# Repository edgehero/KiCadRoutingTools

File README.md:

# gpm campaign assets: 20 boards through `/plan-pcb-placement full` on KiCadRoutingTools main bda59fa0

Results are in discussion #118 (drandyhaas/KiCadRoutingTools). This branch holds what the post links to.

- `media/NN_STEM/`: per board:
  - the movie3d films (`film_seed.*`, the kept seed's anneal; `film_flow.*`, the whole run, where it tells the run's story);
  - the 3D stills, and the human-vs-ours placement comparisons;
  - the teammate's `REPORT.md`, `TOOL_GAPS.md` and `CHOSEN.json`;
  - what it was given (`README.md`);
  - my grades (`summary.json`, `grade_ours.json`, `board_score.json`);
  - the delivered board.
- `media/_superseded/`: the first runs of daplink and steppenprobe, which were re-run after the audit.
- `wk/gpm/`: every `wk/gpm/...` path the findings and issues cite, at the same path. Copy `wk/` into a checkout at bda59fa0 and run the repro commands from the root.
- `FINDINGS.md`: every verifier verdict (G01-G47, M01-M16). `FINDINGS_CLUSTERED.md` holds the clusters before verification, and `verify/` the batch reports and prompts.
- `old_issues/`: gp14's 65 issues re-checked on main (`OLD_ISSUES.md`, `B1.md`-`B8.md`).
- `AUDIT.md` and `audit/`: the start-state, copying and transcript audit, with its scripts and outputs.
- `issues/`: the issue drafts as filed.
- `staging/`: the campaign scripts (staging, teammate prompt, compare, films, post).
- `GRADE_NOTES.md`, `LAUNCH.md`, `PHASE0.md`, `STAGING_DIFF.md`, `FINDINGS_PREP.md`: the lead's own notes.

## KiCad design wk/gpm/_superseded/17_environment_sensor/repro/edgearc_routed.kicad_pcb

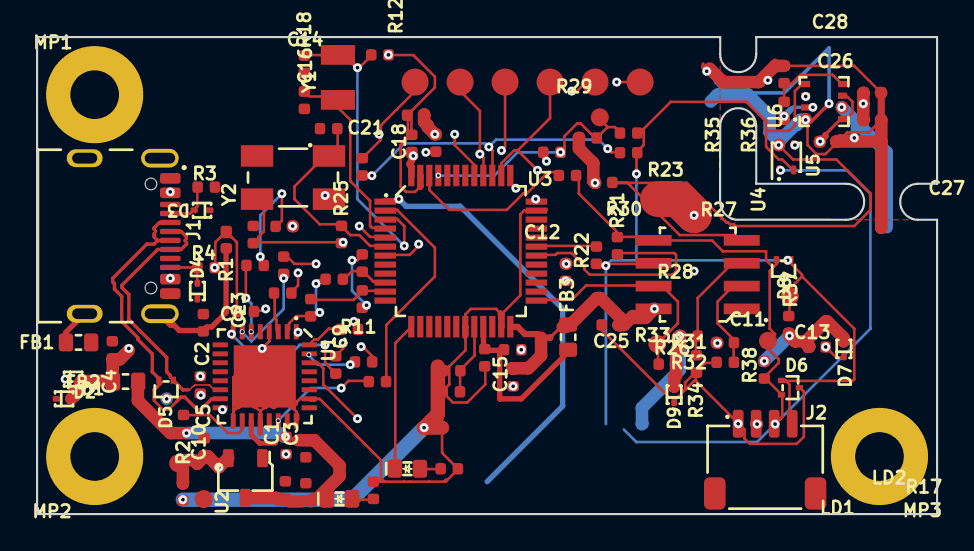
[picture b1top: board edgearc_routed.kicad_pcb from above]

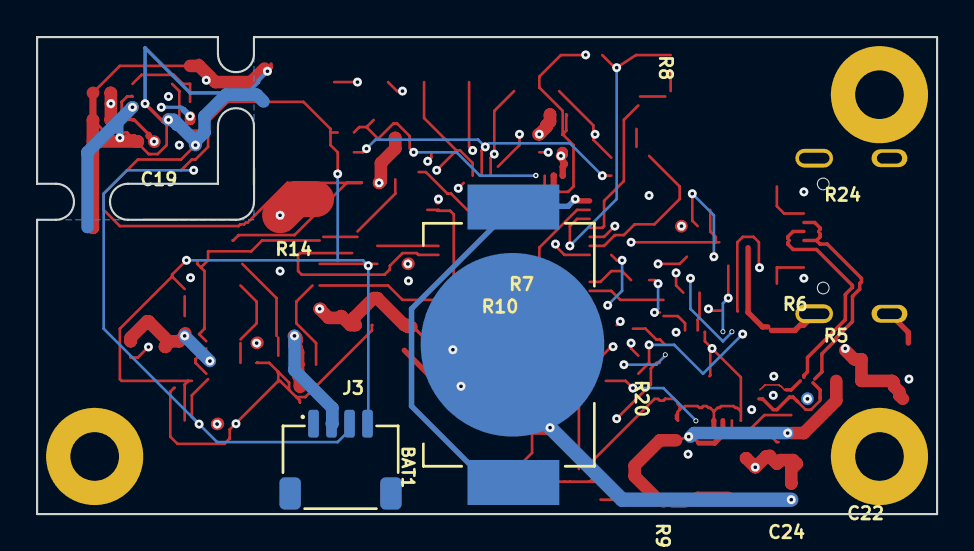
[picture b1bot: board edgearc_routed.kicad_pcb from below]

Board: 4 copper layers, 50.0 x 26.5 mm, 107 parts (2 on the bottom side), 50 nets.

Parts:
BAT1: BAT-HLD-012-SMT-TR; BAT_BAT-HLD-012-SMT-TR
C1, C9, C10: C_4u7_0402; C_0402_1005Metric
C2, C3, C5, C6, C8, C12, C13, C15, C17, C18, C19, C22, C25, C26, C27, C28: C_100n_0402; C_0402_1005Metric
C4, C7, C11, C20, C24: C_2u2_0402; C_0402_1005Metric
C14, C16: C_16p_0402; C_0402_1005Metric
C21, C23: C_10p_0402; C_0402_1005Metric
D1, D2, D3, D4, D7, D9: ESD9X5.0ST5G; SOD-923
D5, D6, D8: TPD2E009_SOT-9X3; SOT-723
FB1, FB2, FB3: FB_120Z_2A_Murata-BLM18PG_0603; FB_0603_1608Metric
J1: USB-C_GCT_USB4105-GF-A; USB-C_Receptacle_GCT_USB4105-GF-A
J2, J3: JST_SH_1x4_SM04B-SRSS-TB-LF-SN; Conn_JST_SH_1x4_SM04B-SRSS-TB-LF-SN
LD1, LD2: LED_G_0603_KP-1608ZGC; LED_0603_1608Metric_G
MP1, MP2, MP3: MP_Pad5.4mm_Drill2.7mm
R1, R18, R25: R_1M_0402; R_0402_1005Metric
R2, R26: R_1k_0402; R_0402_1005Metric
R3, R4, R37, R38: R_5k1_0402; R_0402_1005Metric
R5, R6, R7, R8, R9, R10, R11, R13, R14, R15, R16, R20: R_0R_0402; R_0402_1005Metric
R12, R17: R_470R_0402; R_0402_1005Metric
R19, R24, R29, R30, R31, R32, R33, R34, R35, R36: R_100k_0402; R_0402_1005Metric
R21, R22, R23, R27, R28: R_100R_0402; R_0402_1005Metric
TP1, TP2, TP3, TP4, TP5, TP6: TP_1.5mm_SMD; TP_SMD_1.5mm
TP7, TP8, TP9, TP10, TP11, TP12: TP_1mm_SMD; TP_SMD_1mm
U1: FT232R_QFN; QFN-32-1EP_5x5mm
U2: AP7370-33SA-7; SOT-23-3
U3: STM32G474CET6; LQFP-48_7x7mm_P0.5mm
U4: MB85RC1MTPNF-G; SOP-8_3.9x5.05mm_P1.27mm
U5: SHT45; Sensirion_DFN-4-1.5x1.5x0.5mm_P0.8mm
U6: BME280; LGA-8_2.5x2.5mm_BME280
Y1: Resonator_32.768kHz_ECX-31B; Resonator_SMD_ECS_ECX-31B_3.2x1.5x0.9mm
Y2: Resonator_8MHz_ABM3B; Resonator_SMD_Abracon_ABM3B_5x3.2mm

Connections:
+3V3: C9.2, C10.2, C11.1, C12.2, C13.1, C15.2, C17.2, C18.2, C25.1, C26.1, C27.2, C28.1, D7.2 (A), D9.2 (A), FB3.2, J2.2, J3.2, R19.2, R24.2, R26.2, R29.2, R31.2, R33.2, R35.1, R37.2, R38.2, TP9.1, U2.2 (VOUT), U3.24 (VDD), U3.36 (VDD), U3.48 (VDD), U4.8 (VDD), U5.3 (VDD), U6.2 (CSB), U6.6 (VDDIO), U6.8 (VDD)
+5V: C1.2, C3.2, C7.1, C8.1, FB2.2, LD1.1 (C), R2.1, U1.19 (VCC), U2.3 (VIN)
/FRAM_WP: R26.1, TP7.1, U3.25 (PB11), U4.7 (WP)
/FTDI_USER_PB: R11.2, U3.2 (PC13)
/LD2: LD2.1 (C), U3.13 (PA5)
/OSC32_IN: C14.1, R18.1, U3.3 (PC14-OSC32_IN), Y1.1
/OSC32_OUT: C16.1, R18.2, U3.4 (PC15-OSC32_OUT), Y1.2
/USB_CC1: D3.2 (A), J1.A5 (CC_{1}), R3.2
/USB_CC2: D4.2 (A), J1.B5 (CC_{2}), R4.2
/USB_D_N: D5.2, J1.A7 (D_{A}-), J1.B7 (D_{B}-), U1.15 (USBDM)
/USB_D_P: D5.1, J1.A6 (D_{A}+), J1.B6 (D_{B}+), U1.14 (USBDP)
/VBUS: C4.2, D1.2 (A), D2.2 (A), FB2.1, J1.A4 (VBUS), J1.A9 (VBUS), J1.B4 (VBUS), J1.B9 (VBUS)
GND: BAT1.N, C1.1, C2.1, C3.1, C4.1, C5.1, C6.1, C7.2, C8.2, C9.1, C10.1, C11.2, C12.1, C13.2, C14.2, C15.1, C16.2, C17.1, C18.1, C19.2, C20.1, C21.1, C22.2, C23.1, C24.1, C25.2, C26.2, C27.1, C28.2, D1.1 (C), D2.1 (C), D3.1 (C), D4.1 (C), D5.3, D6.3, D7.1 (C), D8.3, D9.1 (C), FB1.2, J1.A1 (GND), J1.A12 (GND), J1.B1 (GND), J1.B12 (GND), J2.1, J3.1, R1.2, R3.1, R4.1, R12.1, R17.1, R30.1, R32.1, R34.1, R36.1, TP10.1, U1.4 (GND), U1.17 (GND), U1.20 (GND), U1.24 (AGND), U1.26 (TEST), U1.33 (EP), U2.1 (GND), U3.19 (VSSA), U3.23 (VSS), U3.35 (VSS), U3.47 (VSS), U4.4 (VSS), U5.4 (VSS), U6.1 (GND), U6.7 (GND), Y2.2 (SH), Y2.4 (SH)
GNDREF: C2.2, FB1.1, J1.SH, R1.1
I2C_1_SCL: D6.1, D8.1, J2.4, J3.4, R22.2, R23.2, R27.2, R37.1, TP12.1, U4.6 (SCL), U5.2 (SCL), U6.4 (SCK)
I2C_1_SDA: D6.2, D8.2, J2.3, J3.3, R21.2, R28.2, R38.1, TP11.1, U4.5 (SDA), U5.1 (SDA), U6.3 (SDI)
JTDI: R10.2, R20.1, TP6.1
JTDO: R9.2, TP5.1, U3.40 (PB3)
JTRST: R7.2, R24.1, TP2.1, U3.41 (PB4)
LPUART_1_STM_RX: R13.2, R16.2, U3.11 (PA3)
LPUART_1_STM_TX: R14.2, R15.2, U3.10 (PA2)
NRST: R8.2, R19.1, TP1.1, U3.7 (PG10-NRST)
unnamed: LD1.2 (A), R12.2
unnamed: LD2.2 (A), R17.2
unnamed: C5.2, C6.2, U1.1 (VCCIO), U1.16 (3V3OUT)
unnamed: R11.1, U1.22 (CBUS0)
unnamed: R9.1, U1.8 (CTS#)
unnamed: R8.1, U1.7 (DCD#)
unnamed: R7.1, U1.6 (DSR#)
unnamed: R5.1, U1.31 (DTR#)
unnamed: R2.2, U1.18 (RESET#)
unnamed: R10.1, U1.3 (RI#)
unnamed: R6.1, U1.32 (RTS#)
unnamed: R14.1, R16.1, U1.2 (RXD)
unnamed: R13.1, R15.1, U1.30 (TXD)
unnamed: R21.1, U3.30 (PA8)
unnamed: R22.1, U3.31 (PA9)
unnamed: R20.2, R23.1, U3.39 (PA15)
unnamed: R27.1, R29.1, R30.2, TP8.1, U3.45 (PB8-BOOT0)
unnamed: R28.1, U3.46 (PB9)
unnamed: C23.2, R25.2, U3.5 (PF0-OSC_IN), Y2.3
unnamed: C21.2, R25.1, U3.6 (PF1-OSC_OUT), Y2.1
unnamed: BAT1.P1, BAT1.P2, U3.1 (VBAT)
unnamed: C19.1, C20.2, FB3.1, U3.21 (VDDA)
unnamed: C22.1, C24.2, U3.20 (VREF+)
unnamed: R31.1, R32.2, U4.2 (A1)
unnamed: R33.1, R34.2, U4.3 (A2)
unnamed: R35.2, R36.2, U6.5 (SDO)
SWCLK-JTCK: R6.2, TP4.1, U3.38 (PA14)
SWDIO-JTMS: R5.2, TP3.1, U3.37 (PA13)

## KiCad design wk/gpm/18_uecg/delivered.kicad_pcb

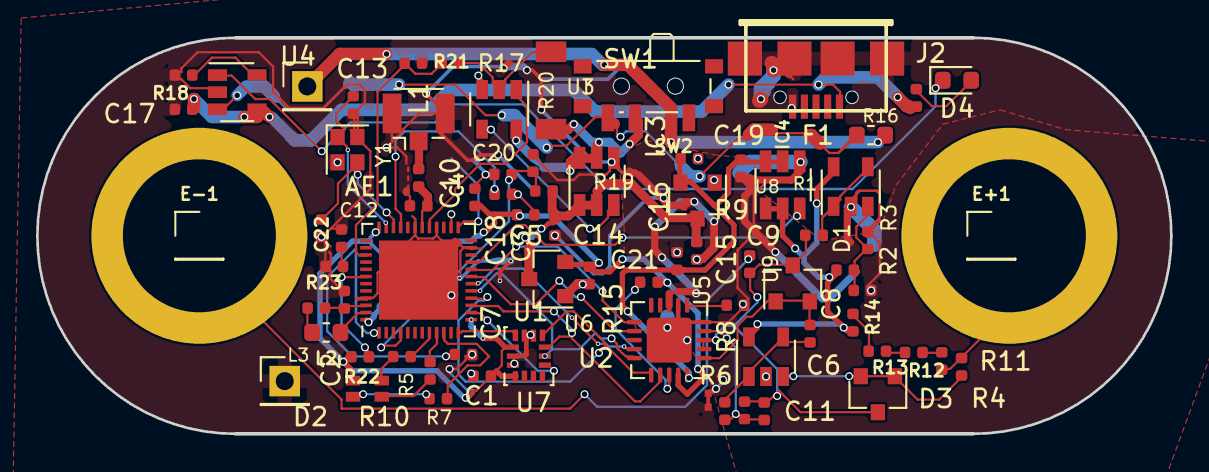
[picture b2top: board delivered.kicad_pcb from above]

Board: 2 copper layers, 63.0 x 22.0 mm, 75 parts (1 on the bottom side), 59 nets.

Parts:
AE1: Antenna_Shield; U.FL_Hirose_U.FL-R-SMT-1_Vertical
C1, C4, C7, C8, C15, C16, C20, C22: 100 nF; C_0402_1005Metric
C2, C14, C17, C18, C19, C21: 2.2 uF; C_0402_1005Metric
C3: 100 pF; C_0402_1005Metric
C5, C6, C9: 10 uF; C_0402_1005Metric
C10: 0.8 pF; C_0402_1005Metric
C11: 10 nF; C_0402_1005Metric
C12, C13: 12 pF; C_0402_1005Metric
D1, D3: BAV99-E3-08; SOT-23
D2: LED_BGRA; LED_RGB_0603_a4
D4: LED GREEN; LED_0603_1608Metric
E+1: Conn_01x01_Male; PinHeader_1x01_P2.54mm_Vertical
E-1: Conn_01x01_Male; PinHeader_1x01_P2.54mm_Vertical
F1: PTC Fuse 0.25A; Fuse_0603_1608Metric
GC1: GND_CONN; 0R_SHUNT
IC3, IC4: SIP32510DT-T1-GE3; TSOT-23-6
J2: USB_B_Micro; conn_usb_B_micro_smd_our
J5: Conn_01x01_Male; Pin_Header_Straight_1x01_Pitch2.54mm
J6: Conn_01x01_Male; PinHeader_1x01_P2.54mm_Vertical
L1: 3.9 nH; L_0402_1005Metric
L2: 10 uH; L_0603_1608Metric
L3: 15 nH; L_0402_1005Metric
R1: 10R; R_0402_1005Metric
R2: 510k; R_0402_1005Metric
R3, R15, R19: 200k; R_0402_1005Metric
R4, R9, R20, R21, R23: 100k; R_0402_1005Metric
R5, R7, R10, R16: 2k; R_0402_1005Metric
R6, R17: 22k; R_0402_1005Metric
R8: 10k; R_0402_1005Metric
R11, R12, R13, R14: 10М; R_0402_1005Metric
R18: 8.2k; R_0402_1005Metric
R22: 100k NTC; R_0402_1005Metric
SC1: SWD_POGO
SW1: SW_Push; BTN_HY_1185
SW2: SW_SPDT; SW_SPDT_PCM12
U1: nRF52832-QFxx; QFN-48-1EP_6x6mm_Pitch0.4mm
U2: MCP3911(QFN); QFN-20-1EP_4x4mm_P0.5mm_EP2.5x2.5mm
U3: 74AHC1G32; SOT-23-5
U4: TP4054_replacement_for_MCP73831-2-OT; SOT-23-5
U5: XC6206P302MR_SOT23; SOT-23
U6: XC6206P332MR_SOT23; SOT-23
U7: LSM6DS3; LGA-14_3x2.5mm_P0.5mm_fix
U8, U9: TLV271CW5; SOT-23-5
Y1: 32MHz; Crystal_SMD_2016-4Pin_2.0x1.6mm

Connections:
+3.3VA: IC4.1 (OUT_1), IC4.2 (OUT_2), R2.2, R14.2, U8.5 (V+), U9.5 (V+)
+3.3VADC: C9.2, C16.2, C19.2, IC4.5 (IN_1), IC4.6 (IN_2), U2.20 (AVdd), U5.2 (VO)
+3V3: C4.1, C5.2, C7.2, C14.2, D2.4 (A), R15.2, R22.1, SC1.2 (3V3), U1.13 (VDD), U1.36 (VDD), U1.48 (VDD), U2.19 (DVdd), U6.2 (VO), U7.5 (VDDIO), U7.8 (VDD)
+4V: IC3.5 (IN_1), IC3.6 (IN_2), SW1.2, SW2.2 (B), U3.5 (VCC)
+BATT: C18.2, C21.2, IC3.1 (OUT_1), IC3.2 (OUT_2), R19.1, U5.3 (VI), U6.3 (VI)
AMP_EN: IC4.3 (EN), U1.21 (P0.18/SWO)
BATT_LEVEL: C20.2, R19.2, R20.1, U1.4 (P0.02/AIN0)
BT_OUT: R17.1, SW1.1, U3.2
CH0+: C6.2, D1.1 (A), D1.2 (K), U2.1 (CH0+)
CH0-: C11.2, D1.3 (A), D3.3 (A), R1.1, R8.1, R9.1, U2.2 (CH0-), U2.3 (CH1-)
CH1+: C11.1, R6.1, R8.2, U2.4 (CH1+)
CIPO: U1.16 (P0.13), U2.16 (MISO), U7.1 (SDO/SA0)
COPI: U1.15 (P0.12), U2.17 (MOSI), U7.14 (SDA)
CS: U1.18 (P0.15), U2.14 (CS)
DR: U1.20 (P0.17), U2.11 (DR)
F_CLK: U1.19 (P0.16), U2.12 (OSC1/CLK)
GND: AE1.2 (Shield), C1.2, C2.2, C3.2, C4.2, C5.1, C7.1, C10.2, C12.1, C13.1, C14.1, C17.1, C18.1, C20.1, C21.1, C22.1, GC1.1, IC3.4 (GND), J2.5 (GND), J2.6 (Shield), J6.1, R18.2, R20.2, R21.2, R23.2, SC1.1 (GND), U1.23 (P0.20), U1.28 (P0.23), U1.31 (VSS), U1.45 (VSS), U1.49 (VSS), U2.8 (Dgnd), U3.3 (GND), U4.2 (VSS), U6.1 (GND), U7.2 (SDX), U7.3 (SCX), U7.6 (GND), U7.7 (GND), Y1.2, Y1.4
GNDA: C8.1, C9.1, C15.1, C16.1, C19.1, GC1.2, IC4.4 (GND), R3.1, U2.5 (Agnd), U2.7 (REFIN-), U2.21 (EP), U5.1 (GND), U8.2 (V-), U9.2 (V-)
IN2: D3.1 (A), D3.2 (K), R4.1, U9.3 (+)
LSM_CS: U1.14 (P0.11), U7.12 (CS)
LSM_INT: U1.12 (NFC2/P0.10), U7.4 (INT1)
NTC_REF: C22.2, R22.2, R23.1, U1.42 (P0.30/AIN6)
unnamed: AE1.1 (A), L1.1
unnamed: C1.1, U1.1 (DEC1)
unnamed: C2.1, L3.2, U1.46 (DEC4)
unnamed: C3.1, U1.33 (DEC3)
unnamed: C6.1, R6.2, U9.1, U9.4 (-)
unnamed: C8.2, R2.1, R3.2, U8.3 (+)
unnamed: C10.1, L1.2, U1.30 (ANT)
unnamed: C12.2, U1.34 (XC1), Y1.3
unnamed: C13.2, U1.35 (XC2), Y1.1
unnamed: C15.2, U2.6 (REFIN+)
unnamed: C17.2, J2.1 (VBUS), R16.2, U4.4 (VDD)
unnamed: D2.1 (BK), R10.1
unnamed: D2.2 (GK), R7.1
unnamed: D2.3 (RK), R5.1
unnamed: D4.1 (K), U4.1 (STAT)
unnamed: D4.2 (A), R16.1
unnamed: E+1.1, R4.2, R11.1
unnamed: E-1.1, R9.2
unnamed: F1.1, SW2.3 (C), U4.3 (VBAT)
unnamed: F1.2, J5.1
unnamed: IC3.3 (EN), U3.4
unnamed: L2.1, U1.47 (DCC)
unnamed: L2.2, L3.1
unnamed: R1.2, U8.1, U8.4 (-)
unnamed: R5.2, U1.8 (P0.06)
unnamed: R7.2, U1.9 (P0.07)
unnamed: R10.2, U1.10 (P0.08)
unnamed: R11.2, R12.1
unnamed: R12.2, R13.1
unnamed: R13.2, R14.1
unnamed: R15.1, U2.18 (RESET)
unnamed: R17.2, R21.1, U1.39 (P0.27)
unnamed: R18.1, U4.5 (PROG)
SCLK: U1.17 (P0.14), U2.15 (SCK), U7.13 (SCL)
SWDCLK: SC1.4 (SWDCLK), U1.25 (SWDCLK)
SWDIO: SC1.3 (SWDIO), U1.26 (SWDIO)
SYS_ON: U1.29 (P0.24), U3.1

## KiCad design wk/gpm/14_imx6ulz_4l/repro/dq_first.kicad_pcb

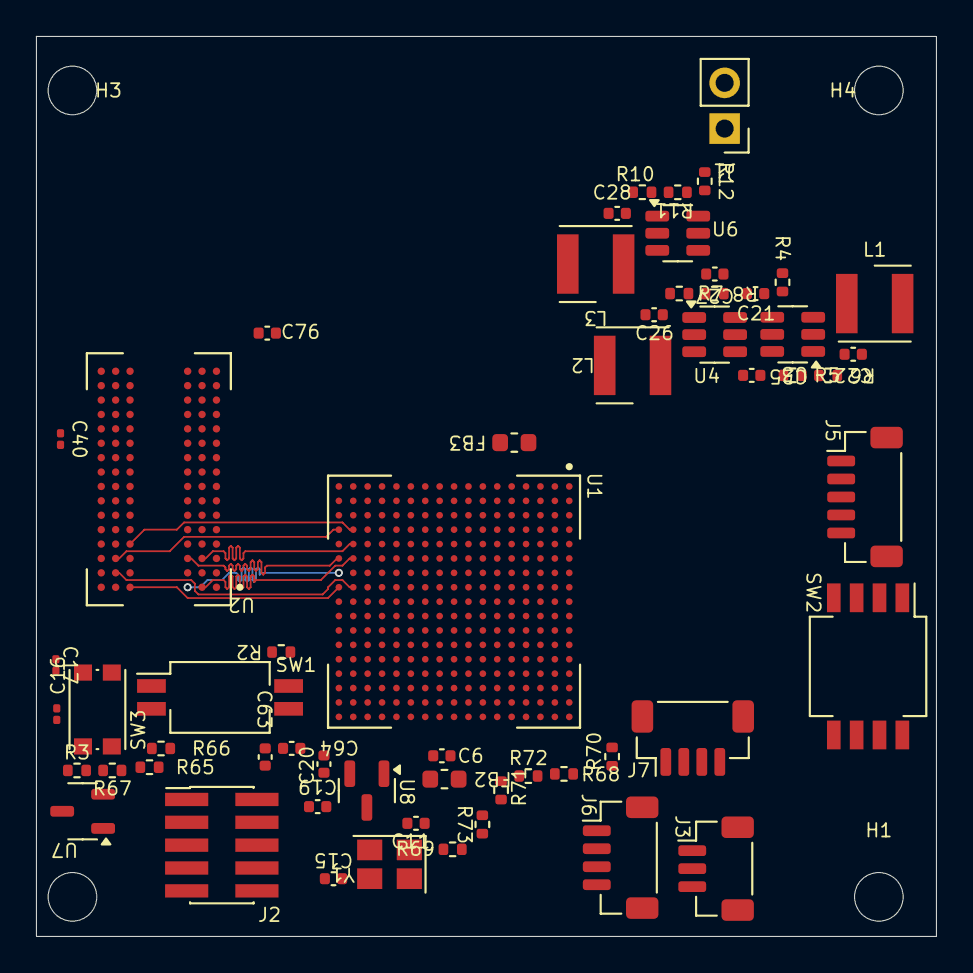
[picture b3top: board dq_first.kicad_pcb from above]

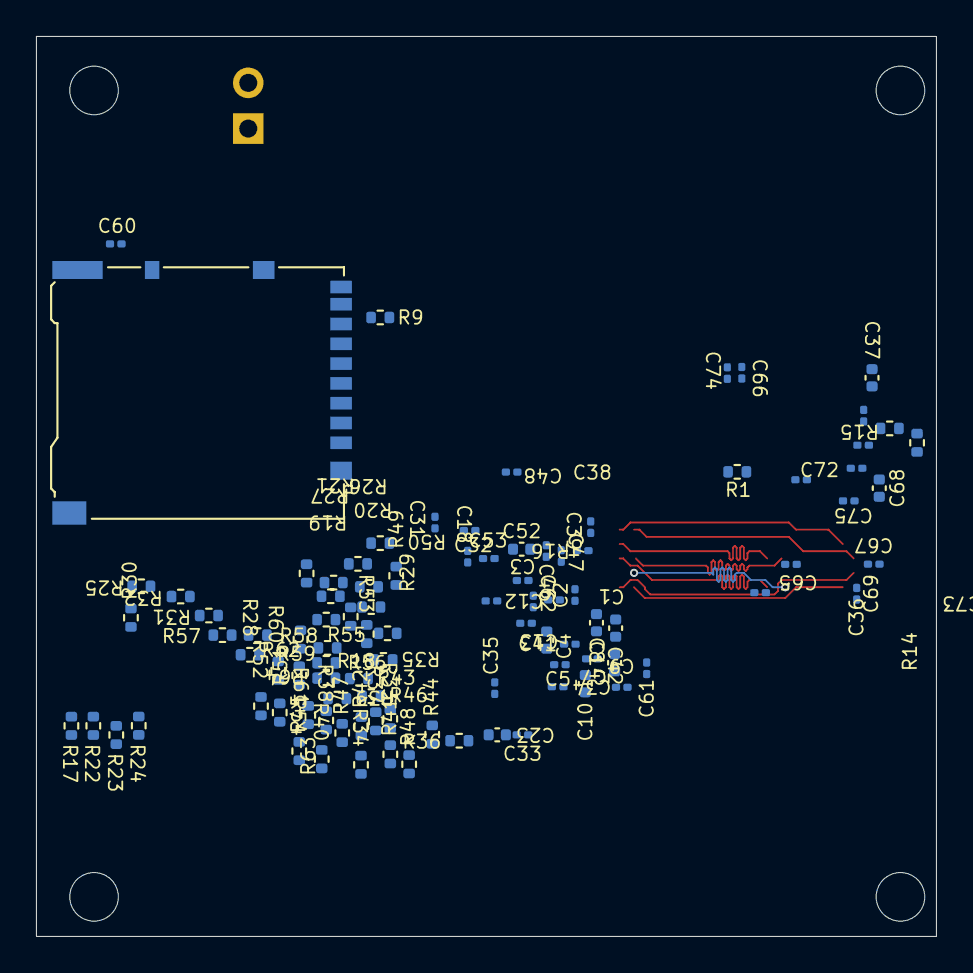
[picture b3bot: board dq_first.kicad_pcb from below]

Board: 4 copper layers, 50.0 x 50.0 mm, 159 parts (97 on the bottom side), 134 nets.

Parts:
C1, C2, C3, C5, C7, C9, C12, C13, C16, C17, C18, C31, C32, C33, C34, C35, C36, C38, C39, C40, C41, C46, C47, C48, C53, C60, C61, C62, C65, C66, C67, C69, C72, C73, C74, C75: 0.22u; C_0201_0603Metric
C4, C8, C23, C26, C28, C63, C68, C76: 22uF/20%/X5R/6.3V; C_0402_1005Metric
C6, C21, C25, C27, C37, C64: 4.7u; C_0402_1005Metric
C10, C42, C52: 10u; C_0402_1005Metric
C11, C15: 18p; C_0402_1005Metric
C14: 0.1u; C_0402_1005Metric
C19, C20: 1u; C_0402_1005Metric
C22: 10uF; C_0402_1005Metric
FB2, FB3: 120ohm@100MHz (2A); L_0603_1608Metric
H1, H2, H3, H4: MountingHole; MountingHole_2.7mm_M2.5
J1: Conn_01x02_Pin; PinHeader_1x02_P2.54mm_Vertical
J2: Conn_ARM_JTAG_SWD_10; PinHeader_2x05_P1.27mm_Vertical_SMD
J3: JST_BM03B-SRSS-TB; JST_SH_BM03B-SRSS-TB_1x03-1MP_P1.00mm_Vertical
J4: Micro_SD_Card_Det_Hirose_DM3AT; microSD_HC_Hirose_DM3AT-SF-PEJM5
J5: JST_BM05B-SRSS-TB; JST_SH_BM05B-SRSS-TB_1x05-1MP_P1.00mm_Vertical
J6, J7: JST_BM04B-SRSS-TB; JST_SH_BM04B-SRSS-TB_1x04-1MP_P1.00mm_Vertical
L1, L2, L3: 2.2uH; L_Wurth_WE-LQSH-4020
R1: 470R; R_0402_1005Metric
R2, R4, R9, R12, R25, R26, R27, R28, R29, R30, R31, R32, R33, R34, R35, R36, R37, R38, R39, R40, R41, R42, R43, R44, R45, R46, R47, R48, R49, R50, R51, R52, R53, R54, R55, R56, R57, R58, R59, R60, R61, R62, R63, R64, R65, R66: 10k; R_0402_1005Metric
R3, R17, R18, R19, R20, R21, R22, R23, R24: 1k; R_0402_1005Metric
R5, R8, R11, R67: 100k; R_0402_1005Metric
R6: 549k; R_0402_1005Metric
R7: 113k; R_0402_1005Metric
R10: 124k; R_0402_1005Metric
R13, R14, R71: 1.5k; R_0402_1005Metric
R15, R16: 240R; R_0201_0603Metric
R68, R69, R72, R73: 22R/R0402; R_0402_1005Metric
R70: 1.5K; R_0402_1005Metric
SW1: SW_DIP_x02; SW_DIP_SPSTx02_Slide_Copal_CHS-02B_W7.62mm_P1.27mm
SW2: SW_DIP_x04; SW_DIP_SPSTx04_Slide_Copal_CHS-04B_W7.62mm_P1.27mm
SW3: SW_Push; SW_Push_1P1T_NO_CK_KMR2
U1: MCIMX6Z0DVM09AB; BGA289C80P17X17_1400X1400X132
U2: K4B4G1646E-BCNB; BGA96C80P6X16_800X1400X120
U4, U5, U6: TLV62568DDC; SOT-23-6
U7: LM809; SOT-23-3
U8: MCP1700x-330xxTT; SOT-23
Y1: Crystal_GND24; Crystal_SMD_SeikoEpson_TSX3225-4Pin_3.2x2.5mm

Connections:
+1V2: C26.1, FB3.1, L2.2, R7.1, R9.1
+3V3: C16.1, C18.1, C22.1, C31.1, C32.1, C33.1, C34.1, C35.1, C60.1, FB2.1, J2.1 (VTref), J4.4 (VDD), J6.1, J7.3, L1.2, R2.2, R4.1, R6.1, R17.2, R18.2, R19.2, R20.2, R21.2, R22.2, R23.2, R24.2, R41.2, R42.2, R43.2, R44.2, R45.2, R46.2, R47.2, R48.2, R49.2, R51.2, R53.2, R55.2, R57.2, R59.2, R61.2, R63.2, R65.2, R66.2, R70.2, R71.2, U1.C4 (NVCC_SD1), U1.E7 (NVCC_NAND), U1.E13 (NVCC_GPIO3), U1.F4 (NVCC_SD2), U1.F13 (NVCC_KPP), U1.H13 (NVCC_UART), U1.J13 (NVCC_GPIO), U7.3 (VCC)
+5V: C19.1, C21.1, C25.1, C27.1, J1.1, U4.4 (VIN), U5.4 (VIN), U6.4 (VIN), U8.3 (VI)
/Boot Config, Clock, Reset/BOOT_CFG1_0: R25.2, SW2.1, U1.B9 (GPIO3_IO05)
/Boot Config, Clock, Reset/BOOT_CFG1_0_SW: R17.1, SW2.8
/Boot Config, Clock, Reset/BOOT_CFG1_1: R18.1, R26.2, U1.A9 (GPIO3_IO06)
/Boot Config, Clock, Reset/BOOT_CFG1_2: R19.1, R27.2, U1.E10 (GPIO3_IO07)
/Boot Config, Clock, Reset/BOOT_CFG1_3: R20.1, R28.2, U1.D10 (GPIO3_IO08)
/Boot Config, Clock, Reset/BOOT_CFG1_4: R21.1, R29.2, U1.C10 (GPIO3_IO09)
/Boot Config, Clock, Reset/BOOT_CFG1_5: R30.2, SW2.2, U1.B10 (GPIO3_IO10)
/Boot Config, Clock, Reset/BOOT_CFG1_5_SW: R22.1, SW2.7
/Boot Config, Clock, Reset/BOOT_CFG1_6: R31.2, SW2.3, U1.A10 (GPIO3_IO11)
/Boot Config, Clock, Reset/BOOT_CFG1_6_SW: R23.1, SW2.6
/Boot Config, Clock, Reset/BOOT_CFG1_7: R32.2, SW2.4, U1.D11 (GPIO3_IO12)
/Boot Config, Clock, Reset/BOOT_CFG1_7_SW: R24.1, SW2.5
/Boot Config, Clock, Reset/BOOT_CFG2_0: R49.1, R50.2, U1.B11 (GPIO3_IO13)
/Boot Config, Clock, Reset/BOOT_CFG2_1: R51.1, R52.2, U1.A11 (GPIO3_IO14)
/Boot Config, Clock, Reset/BOOT_CFG2_2: R53.1, R54.2, U1.E12 (GPIO3_IO15)
/Boot Config, Clock, Reset/BOOT_CFG2_3: R55.1, R56.2, U1.D12 (GPIO3_IO16)
/Boot Config, Clock, Reset/BOOT_CFG2_4: R57.1, R58.2, U1.C12 (GPIO3_IO17)
/Boot Config, Clock, Reset/BOOT_CFG2_5: R59.1, R60.2, U1.B12 (GPIO3_IO18)
/Boot Config, Clock, Reset/BOOT_CFG2_6: R61.1, R62.2, U1.A12 (GPIO3_IO19)
/Boot Config, Clock, Reset/BOOT_CFG2_7: R63.1, R64.2, U1.D13 (GPIO3_IO20)
/Boot Config, Clock, Reset/BOOT_CFG4_0: R33.2, R41.1, U1.C13 (GPIO3_IO21)
/Boot Config, Clock, Reset/BOOT_CFG4_1: R34.2, R42.1, U1.B13 (GPIO3_IO22)
/Boot Config, Clock, Reset/BOOT_CFG4_2: R35.2, R43.1, U1.A13 (GPIO3_IO23)
/Boot Config, Clock, Reset/BOOT_CFG4_3: R36.2, R44.1, U1.D14 (GPIO3_IO24)
/Boot Config, Clock, Reset/BOOT_CFG4_4: R37.2, R45.1, U1.C14 (GPIO3_IO25)
/Boot Config, Clock, Reset/BOOT_CFG4_5: R38.2, R46.1, U1.B14 (GPIO3_IO26)
/Boot Config, Clock, Reset/BOOT_CFG4_6: R39.2, R47.1, U1.A14 (GPIO3_IO27)
/Boot Config, Clock, Reset/BOOT_CFG4_7: R40.2, R48.1, U1.B16 (GPIO3_IO28)
/Boot Config, Clock, Reset/BOOT_MODE0: SW1.4, U1.T10 (BOOT_MODE0)
/Boot Config, Clock, Reset/BOOT_MODE1: SW1.3, U1.U10 (BOOT_MODE1)
/Boot Config, Clock, Reset/BOOT_MODE_PU_0: R65.1, SW1.1
/Boot Config, Clock, Reset/BOOT_MODE_PU_1: R66.1, SW1.2
/Boot Config, Clock, Reset/I2C2_SCL: J7.1, R70.1, U1.F17 (I2C2_SCL)
/Boot Config, Clock, Reset/I2C2_SDA: J7.2, R71.1, U1.G13 (I2C2_SDA)
/Boot Config, Clock, Reset/IMX_XI: C11.1, U1.T16 (XTALI), Y1.1
/Boot Config, Clock, Reset/IMX_XO: C15.1, U1.T17 (XTALO), Y1.3
/Boot Config, Clock, Reset/JTAG_TCK: J2.4 (SWDCLK/TCK), U1.M14 (JTAG_TCK)
/Boot Config, Clock, Reset/JTAG_TDI: J2.8 (NC/TDI), U1.N16 (JTAG_TDI)
/Boot Config, Clock, Reset/JTAG_TDO: J2.6 (SWO/TDO), U1.N15 (JTAG_TDO)
/Boot Config, Clock, Reset/JTAG_TMS: J2.2 (SWDIO/TMS), U1.P14 (JTAG_TMS)
/Boot Config, Clock, Reset/NVCC_PLL_OUT: C9.1, C10.1, U1.P13 (NVCC_PLL)
/Boot Config, Clock, Reset/RST_DLY_L: R3.2, R67.1, U7.2 (~RESET)
/Boot Config, Clock, Reset/SOC_ONOFF: R2.1, U1.R8 (ONOFF)
/Boot Config, Clock, Reset/SOC_RST_L: C17.2, R3.1, SW3.1, U1.P8 (POR_B)
/DRAM/DDRCTL_ZQ: R16.1, U1.N4 (DRAM_ZQPAD)
/DRAM/DRAM_AD0: U1.L5 (DRAM_ADDR00), U2.N3 (A0)
/DRAM/DRAM_AD1: U1.H2 (DRAM_ADDR01), U2.P7 (A1)
/DRAM/DRAM_AD2: U1.K1 (DRAM_ADDR02), U2.P3 (A2)
/DRAM/DRAM_AD3: U1.M2 (DRAM_ADDR03), U2.N2 (A3)
/DRAM/DRAM_AD4: U1.K4 (DRAM_ADDR04), U2.P8 (A4)
/DRAM/DRAM_AD5: U1.L1 (DRAM_ADDR05), U2.P2 (A5)
/DRAM/DRAM_AD6: U1.G2 (DRAM_ADDR06), U2.R8 (A6)
/DRAM/DRAM_AD7: U1.H4 (DRAM_ADDR07), U2.R2 (A7)
/DRAM/DRAM_AD8: U1.J4 (DRAM_ADDR08), U2.T8 (A8)
/DRAM/DRAM_AD9: U1.L2 (DRAM_ADDR09), U2.R3 (A9)
/DRAM/DRAM_AD10: U1.M4 (DRAM_ADDR10), U2.L7 (A10/AP)
/DRAM/DRAM_AD11: U1.K3 (DRAM_ADDR11), U2.R7 (A11)
/DRAM/DRAM_AD12: U1.L4 (DRAM_ADDR12), U2.N7 (A12/~BC)
/DRAM/DRAM_BA0: U1.M1 (DRAM_SDBA0), U2.M2 (BA0)
/DRAM/DRAM_BA1: U1.H1 (DRAM_SDBA1), U2.N8 (BA1)
/DRAM/DRAM_BA2: U1.K2 (DRAM_SDBA2), U2.M3 (BA2)
/DRAM/DRAM_CAS_L: U1.J2 (DRAM_CAS_B), U2.K3 (~CAS)
/DRAM/DRAM_CKE: U1.M3 (DRAM_SDCKE0), U2.K9 (CKE)
/DRAM/DRAM_CLK0_N: R1.2, U1.P2 (DRAM_SDCLK0_N), U2.K7 (~CK)
/DRAM/DRAM_CLK0_P: R1.1, U1.P1 (DRAM_SDCLK0_P), U2.J7 (CK)
/DRAM/DRAM_CS0_L: U1.N2 (DRAM_CS0_B), U2.L2 (~CS)
/DRAM/DRAM_DQ0: U1.T4 (DRAM_DATA00), U2.D7 (DQ8)
/DRAM/DRAM_DQ1: U1.U6 (DRAM_DATA01), U2.C3 (DQ9)
/DRAM/DRAM_DQ2: U1.T6 (DRAM_DATA02), U2.A2 (DQ13)
/DRAM/DRAM_DQ3: U1.U7 (DRAM_DATA03), U2.A3 (DQ15)
/DRAM/DRAM_DQ4: U1.U8 (DRAM_DATA04), U2.A7 (DQ12)
/DRAM/DRAM_DQ5: U1.T8 (DRAM_DATA05), U2.B8 (DQ14)
/DRAM/DRAM_DQ6: U1.T5 (DRAM_DATA06), U2.C2 (DQ11)
/DRAM/DRAM_DQ7: U1.U4 (DRAM_DATA07), U2.C8 (DQ10)
/DRAM/DRAM_DQ8: U1.U2 (DRAM_DATA08), U2.E3 (DQ0)
/DRAM/DRAM_DQ9: U1.U3 (DRAM_DATA09), U2.F2 (DQ2)
/DRAM/DRAM_DQ10: U1.U5 (DRAM_DATA10), U2.G2 (DQ6)
/DRAM/DRAM_DQ11: U1.R4 (DRAM_DATA11), U2.F8 (DQ3)
/DRAM/DRAM_DQ12: U1.P5 (DRAM_DATA12), U2.F7 (DQ1)
/DRAM/DRAM_DQ13: U1.P3 (DRAM_DATA13), U2.H3 (DQ4)
/DRAM/DRAM_DQ14: U1.R2 (DRAM_DATA14), U2.H8 (DQ5)
/DRAM/DRAM_DQ15: U1.R1 (DRAM_DATA15), U2.H7 (DQ7)
/DRAM/DRAM_DQM0: U1.T7 (DRAM_DQM0), U2.D3 (UDM)
/DRAM/DRAM_DQM1: U1.T3 (DRAM_DQM1), U2.E7 (LDM)
/DRAM/DRAM_DQS0_N: U1.P7 (DRAM_SDQS0_N), U2.B7 (~UDQS)
/DRAM/DRAM_DQS0_P: U1.P6 (DRAM_SDQS0_P), U2.C7 (UDQS)
/DRAM/DRAM_DQS1_N: U1.T2 (DRAM_SDQS1_N), U2.G3 (~LDQS)
/DRAM/DRAM_DQS1_P: U1.T1 (DRAM_SDQS1_P), U2.F3 (LDQS)
/DRAM/DRAM_ODT: U1.N1 (DRAM_ODT0), U2.K1 (ODT)
/DRAM/DRAM_RAS_L: U1.M5 (DRAM_RAS_B), U2.J3 (~RAS)
/DRAM/DRAM_RST_L: U1.G4 (DRAM_RESET), U2.T2 (~RESET)
/DRAM/DRAM_VREF: C36.2, C38.1, C39.1, C40.1, R13.2, R14.1, U1.P4 (DRAM_VREF), U2.H1 (VREFDQ), U2.M8 (VREFCA)
/DRAM/DRAM_WE_L: U1.J1 (DRAM_SDWE_B), U2.L3 (~WE)
/DRAM/DRAM_ZQ: R15.1, U2.L8 (ZQ)
/IO and Peripherals/FTDI_RXD: J3.1, R68.2
/IO and Peripherals/FTDI_TXD: J3.3, R69.2
/IO and Peripherals/QSPIA_CS_L: J5.4, U1.E6 (NAND_DQS)
/IO and Peripherals/QSPIA_D0: J5.1, U1.A3 (NAND_READY_B)
/IO and Peripherals/QSPIA_D1: J5.3, U1.C5 (NAND_CE0_B)
/IO and Peripherals/QSPIA_SCLK: J5.2, U1.D5 (NAND_WP_B)
/IO and Peripherals/UART1_RX: R68.1, U1.K16 (UART1_RX_DATA)
/IO and Peripherals/UART1_TX: R69.1, U1.K14 (UART1_TX_DATA)
/IO and Peripherals/UART2_RX: R72.1, U1.J16 (UART2_RX_DATA)
/IO and Peripherals/UART2_RX_R: J6.2, R72.2
/IO and Peripherals/UART2_TX: R73.1, U1.J17 (UART2_TX_DATA)
/IO and Peripherals/UART2_TX_R: J6.3, R73.2
/SDcard/SD1_CLK: J4.5 (CLK), U1.C1 (SD1_CLK)
/SDcard/SD1_CMD: J4.3 (CMD), U1.C2 (SD1_CMD)
/SDcard/SD1_D0: J4.7 (DAT0), U1.B3 (SD1_DATA0)
/SDcard/SD1_D1: J4.8 (DAT1), U1.B2 (SD1_DATA1)
/SDcard/SD1_D2: J4.1 (DAT2), U1.B1 (SD1_DATA2)
/SDcard/SD1_D3: J4.2 (DAT3/CD), U1.A2 (SD1_DATA3)
/SOC Power/V1P27_FB: R7.2, R8.1, U4.6 (FB)
/SOC Power/V1P27_PG: R9.2, U4.5 (PG)
/SOC Power/V1P27_SW: L2.1, U4.3 (SW)
/SOC Power/V3P3_FB: R5.1, R6.2, U5.6 (FB)
/SOC Power/V3P3_PG: R4.2, U4.1 (EN), U5.5 (PG), U6.1 (EN)
/SOC Power/V3P3_SW: L1.1, U5.3 (SW)
/SOC Power/VDD_ARM_CAP: C12.1, C13.1, C23.1, U1.G9 (VDD_ARM_CAP), U1.G10 (VDD_ARM_CAP__1), U1.G11 (VDD_ARM_CAP__2), U1.H11 (VDD_ARM_CAP__3)
/SOC Power/VDD_ARM_SOC_IN: C61.1, C62.1, C63.1, C64.1, FB3.2, U1.H9 (VDD_SOC_IN), U1.H10 (VDD_SOC_IN__1), U1.J9 (VDD_SOC_IN__2), U1.J10 (VDD_SOC_IN__3), U1.K9 (VDD_SOC_IN__4), U1.K10 (VDD_SOC_IN__5)
/SOC Power/VDD_HIGH_CAP: C7.1, C8.1, U1.R14 (VDD_HIGH_CAP), U1.R15 (VDD_HIGH_CAP__1)
/SOC Power/VDD_HIGH_IN: C5.1, C6.1, FB2.2, U1.L13 (VDD_HIGH_IN), U1.M13 (VDD_HIGH_IN__1), U1.N13 (VDD_HIGH_IN__2)
/SOC Power/VDD_SNVS_CAP: C41.1, U1.N12 (VDD_SNVS_CAP)
/SOC Power/VDD_SNVS_IN: C20.1, U1.P12 (VDD_SNVS_IN), U5.1 (EN), U8.2 (VO)
/SOC Power/VDD_SOC_CAP: C1.1, C2.1, C3.1, C4.1, U1.G8 (VDD_SOC_CAP), U1.H8 (VDD_SOC_CAP__1), U1.J8 (VDD_SOC_CAP__2), U1.J11 (VDD_SOC_CAP__3), U1.K8 (VDD_SOC_CAP__4), U1.K11 (VDD_SOC_CAP__5), U1.L8 (VDD_SOC_CAP__6), U1.L9 (VDD_SOC_CAP__7), U1.L10 (VDD_SOC_CAP__8), U1.L11 (VDD_SOC_CAP__9)
/SOC Power/VDD_USB_CAP: C14.1, C42.1, U1.R12 (VDD_USB_CAP)
/SOC Power/VMEM_FB: R10.2, R11.1, U6.6 (FB)
/SOC Power/VMEM_PG: R12.2, U6.5 (PG)
/SOC Power/VMEM_SW: L3.1, U6.3 (SW)
GND: C1.2, C2.2, C3.2, C4.2, C5.2, C6.2, C7.2, C8.2, C9.2, C10.2, C11.2, C12.2, C13.2, C14.2, C15.2, C16.2, C17.1, C18.2, C19.2, C20.2, C21.2, C22.2, C23.2, C25.2, C26.2, C27.2, C28.2, C31.2, C32.2, C33.2, C34.2, C35.2, C37.2, C38.2, C39.2, C40.2, C41.2, C42.2, C46.2, C47.2, C48.2, C52.2, C53.2, C60.2, C61.2, C62.2, C63.2, C64.2, C65.2, C66.2, C67.2, C68.2, C69.2, C72.2, C73.2, C74.2, C75.2, C76.2, J1.2, J2.3 (GND), J2.5 (GND), J2.9 (GNDDetect), J3.2, J4.6 (VSS), J5.5, J6.4, J7.4, R5.2, R8.2, R11.2, R14.2, R15.2, R16.2, R25.1, R26.1, R27.1, R28.1, R29.1, R30.1, R31.1, R32.1, R33.1, R34.1, R35.1, R36.1, R37.1, R38.1, R39.1, R40.1, R50.1, R52.1, R54.1, R56.1, R58.1, R60.1, R62.1, R64.1, R67.2, SW3.2, U1.A1 (VSS), U1.A17 (VSS__1), U1.C3 (VSS__2), U1.C7 (VSS__3), U1.C11 (VSS__4), U1.C15 (VSS__5), U1.E8 (VSS__6), U1.E11 (VSS__7), U1.F6 (VSS__8), U1.F7 (VSS__9), U1.F8 (VSS_1), U1.F9 (VSS_1__1), U1.F10 (VSS_1__2), U1.F11 (VSS_1__3), U1.F12 (VSS_1__4), U1.G3 (VSS_1__5), U1.G5 (VSS_1__6), U1.G7 (VSS_1__7), U1.G12 (VSS_1__8), U1.G15 (VSS_1__9), U1.H7 (VSS_2), U1.H12 (VSS_2__1), U1.J5 (VSS_2__2), U1.J7 (VSS_2__3), U1.J12 (VSS_2__4), U1.K7 (VSS_2__5), U1.K12 (VSS_2__6), U1.L3 (VSS_2__7), U1.L7 (VSS_2__8), U1.L12 (VSS_2__9), U1.M7 (VSS_3), U1.M8 (VSS_3__1), U1.M9 (VSS_3__2), U1.M10 (VSS_3__3), U1.M11 (VSS_3__4), U1.M12 (NGND_KEL0), U1.N3 (VSS_3__5), U1.N5 (VSS_3__6), U1.N7 (TEST_MODE), U1.R3 (VSS_3__7), U1.R5 (VSS_3__8), U1.R7 (VSS_3__9), U1.R11 (VSS_4), U1.R16 (VSS_4__1), U1.R17 (VSS_4__2), U1.T14 (VSS_4__3), U1.U1 (VSS_4__4), U1.U14 (VSS_4__5), U1.U17 (VSS_4__6), U2.A9 (VSS), U2.B1 (VSSQ), U2.B3 (VSS__1), U2.B9 (VSSQ__1), U2.D1 (VSSQ__2), U2.D8 (VSSQ__3), U2.E1 (VSS__2), U2.E2 (VSSQ__4), U2.E8 (VSSQ__5), U2.F9 (VSSQ__6), U2.G1 (VSSQ__7), U2.G8 (VSS__3), U2.G9 (VSSQ__8), U2.J2 (VSS__4), U2.J8 (VSS__5), U2.M1 (VSS__6), U2.M9 (VSS__7), U2.P1 (VSS__8), U2.P9 (VSS__9), U2.T1 (VSS__10), U2.T9 (VSS__11), U4.2 (GND), U5.2 (GND), U6.2 (GND), U7.1 (GND), U8.1 (GND), Y1.2, Y1.4
VMEM: C28.1, C36.1, C37.1, C46.1, C47.1, C48.1, C52.1, C53.1, C65.1, C66.1, C67.1, C68.1, C69.1, C72.1, C73.1, C74.1, C75.1, C76.1, L3.2, R10.1, R12.1, R13.1, U1.G6 (NVCC_DRAM), U1.H6 (NVCC_DRAM__1), U1.J6 (NVCC_DRAM__2), U1.K6 (NVCC_DRAM__3), U1.L6 (NVCC_DRAM__4), U1.M6 (NVCC_DRAM__5), U2.A1 (VDDQ), U2.A8 (VDDQ__1), U2.B2 (VDD), U2.C1 (VDDQ__2), U2.C9 (VDDQ__3), U2.D2 (VDDQ__4), U2.D9 (VDD__1), U2.E9 (VDDQ__5), U2.F1 (VDDQ__6), U2.G7 (VDD__2), U2.H2 (VDDQ__7), U2.H9 (VDDQ__8), U2.K2 (VDD__3), U2.K8 (VDD__4), U2.N1 (VDD__5), U2.N9 (VDD__6), U2.R1 (VDD__7), U2.R9 (VDD__8)

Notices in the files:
parts and their libraries:
License: Apache-2.0
